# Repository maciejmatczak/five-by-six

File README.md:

# five-by-six
`five-by-six` is a split keyboard design which tries to meet this goals:
- 5x6 keys per half (so [let's split](https://github.com/climbalima/let-s-Split-v2) with a number row)
- dual side pcb
- case design done in parametrical manner, in a CAD software
- high automations/scripting for predictable and reproducible results

## Table of content
- [five-by-six](#five-by-six)
  - [Table of content](#table-of-content)
- [Description](#description)
  - [PCB](#pcb)
  - [Case](#case)
  - [Automations](#automations)
  - [Development setup](#development-setup)
  - [Workflow](#workflow)

# Description
## PCB
PCB is designed in KiCAD with help of 3rd party libraries from [keebio](https://github.com/keebio) (components and footprints). Can't thank enough for battle tested, dual sided switch footprints. Keys are set in matrix of pitch 19.05mm. Arduino Pro Micro is placed on outside edge, jack is placed on the inside.

## Case
Case is designed in FreeCAD to achieve pure mechanical, parametrical description. Exported DXF (Autodesk DXF 2D(\*.dxf)) of every element is later manually imported in a clean KiCad's PCB as edge cuts. After that, every circle is replaced with a proper mounting hole.

Master sketch approach was used, learned with mr Ha Gei's [video](https://www.youtube.com/watch?v=8Bmcgn2RBGI).

## Automations
All the actions are held in `tasks.py` files which are handled by [invoke](http://www.pyinvoke.org/). Case and PCB designs has it's own `tasks.py` which are design specific. Global one is used for creating fabrication files.

Plotting scripts are based on [plotter](https://github.com/akshmakov/pcbops_template/blob/master/kicad_cicd/plotter.py) from [Andrey Shmakov](https://github.com/akshmakov). He also gave a nice talk during KiCon 2019 ([video](https://www.youtube.com/watch?v=cQ-iFtBBwFc)).

`circles_to_holes.py` was created to easily transfer FreeCAD design hole data to mounting holes/drill information.

## Development setup
This software versions was used:
 - KiCad 5.1.2
 - FreeCAD 0.18
 - Python 3.7 (though >= 3.6 should be fine)

Clone the repository, download submodules:
```
git submodule update --init --recursive
```

Under Linux environment (at least for Manjaro and KiCad from official packages) KiCad's python packages are setup for system wide python. The easiest way to install dependencies is to:
```
pip install -r requirements.txt --user
```

Create .env file in root directory with path to KiCad's MountingHole library being set as in example:
```
KICAD_MOUNTING_HOLE_PATH = '/usr/share/kicad/modules/MountingHole.pretty'
```

## Workflow
Short description of step by step procedure of development:
 - case:
   - design case and pcb contour in FreeCAD
   - export designs to DXFs
   - load case DXFs into empty KiCad projects, save, close
   - while being under `five-by-six/case` directory, run `inv circle-to-holes`, which would exchange every circle to proper M2 padded mounting hole
 - pcb:
   - design schematic, open pcb
   - load pcb contour DXF from case design
   - route PCB
   - run `inv circle-to-holes` which would exchange circles to 5mm drill holes (for standoffs)
 - fabrication files
   - in root directory run `inv plot-all`; all gerbers should be plotted, zipped + some basic documentation and preview pdfs created as well

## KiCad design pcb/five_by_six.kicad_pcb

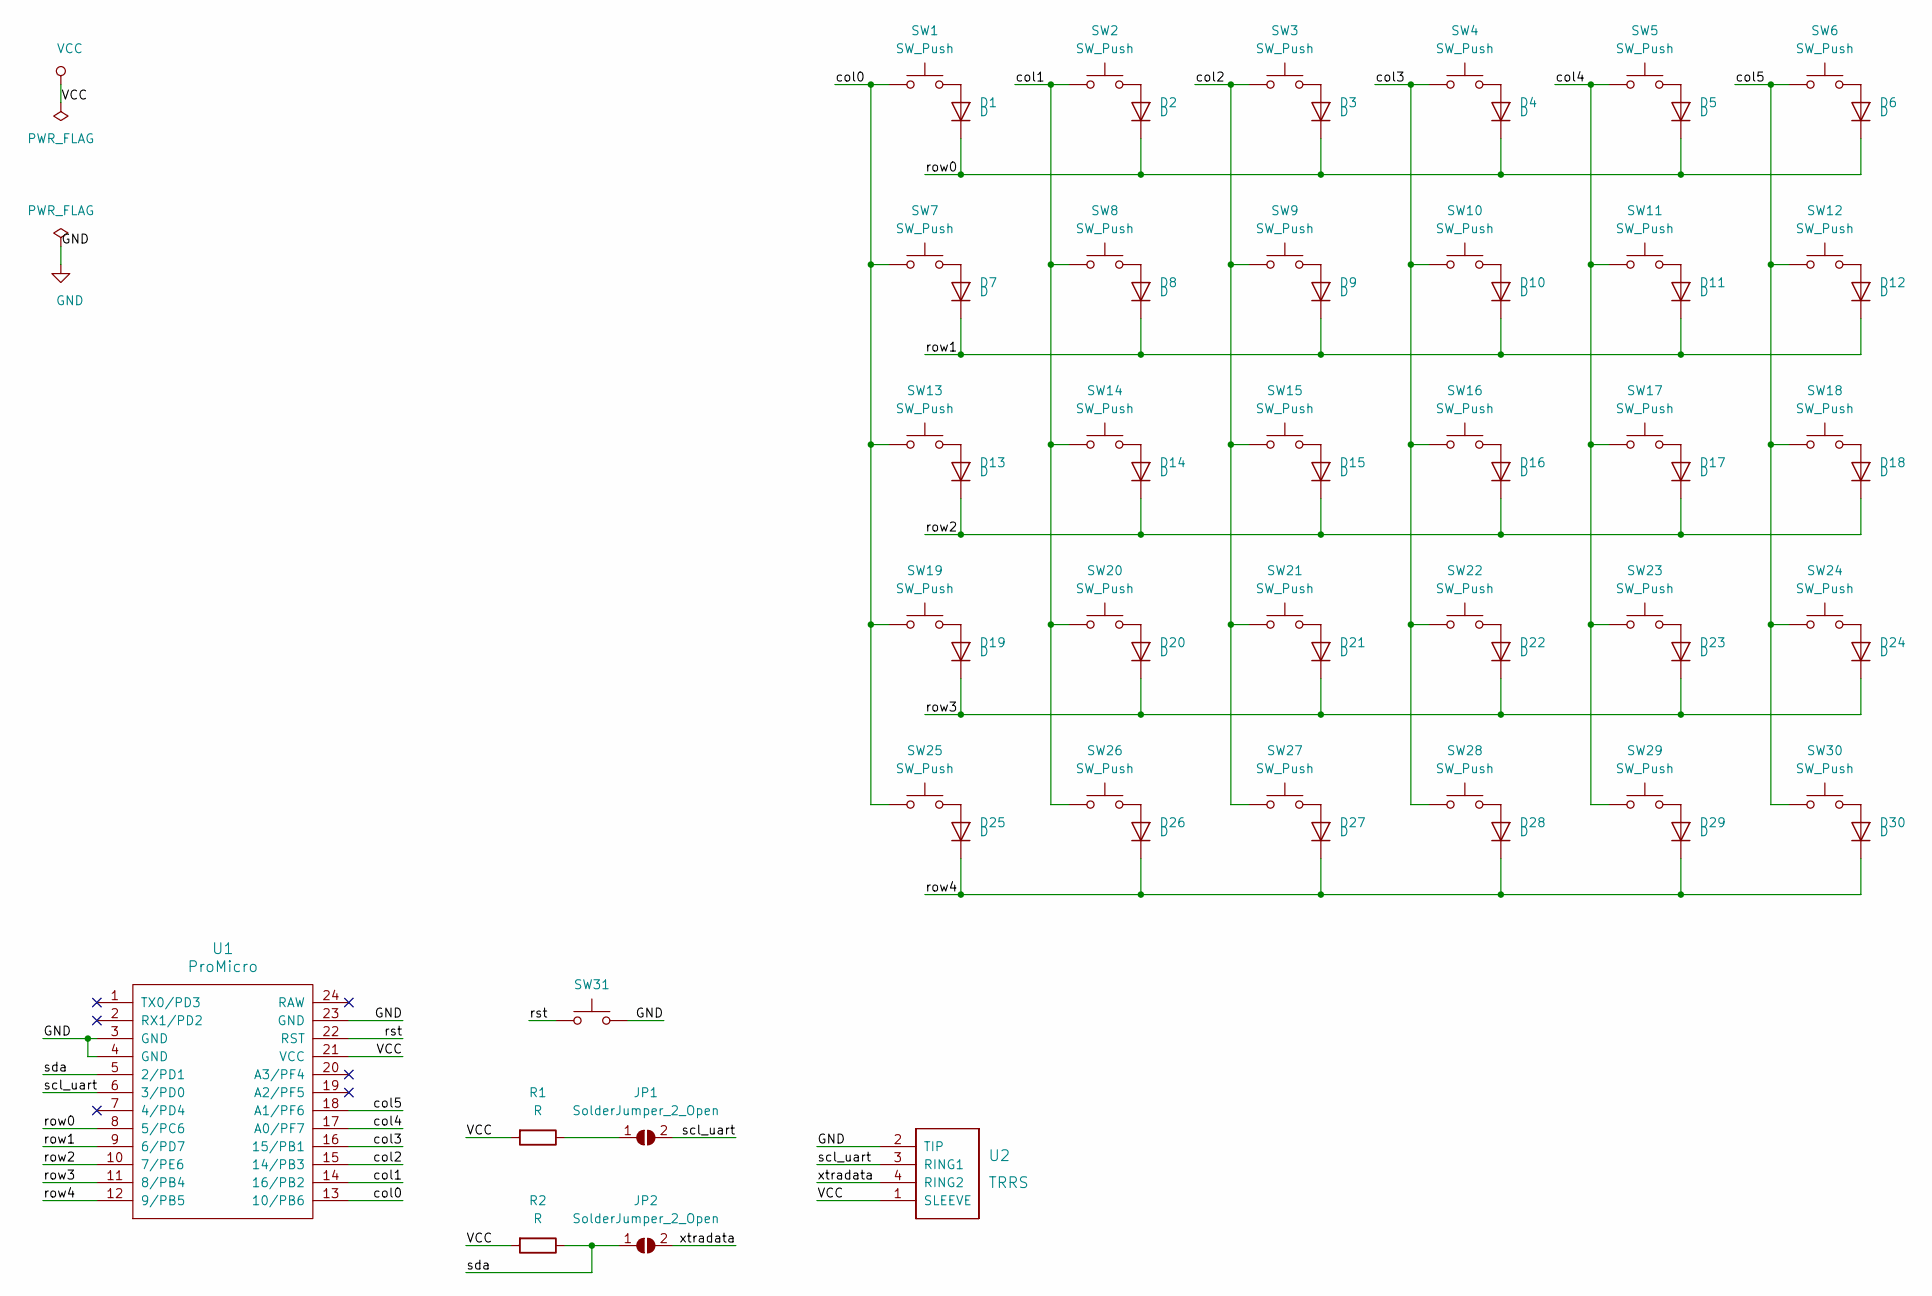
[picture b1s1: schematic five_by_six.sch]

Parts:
D1, D2, D3, D4, D5, D6, D7, D8, D9, D10, D11, D12, D13, D14, D15, D16, D17, D18, D19, D20, D21, D22, D23, D24, D25, D26, D27, D28, D29, D30: D; Diode-dual
JP1, JP2: SolderJumper_2_Open; SolderJumper-2_P1.3mm_Open_RoundedPad1.0x1.5mm
R1, R2: R; Resistor-Hybrid
SW1, SW2, SW3, SW4, SW5, SW6, SW7, SW8, SW9, SW10, SW11, SW12, SW13, SW14, SW15, SW16, SW17, SW18, SW19, SW20, SW21, SW22, SW23, SW24, SW25, SW26, SW27, SW28, SW29, SW30: SW_Push; Hybrid_PCB_100H_Dual_hole
SW31: MX; SW_PUSH_6mm_H7.3mm
U1: ProMicro; ArduinoProMicro
U2: TRRS; TRRS-PJ-320A-dual

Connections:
/col0: SW1.1, SW7.1, SW13.1, SW19.1, SW25.1, U1.13 (10/PB6)
/col1: SW2.1, SW8.1, SW14.1, SW20.1, SW26.1, U1.14 (16/PB2)
/col2: SW3.1, SW9.1, SW15.1, SW21.1, SW27.1, U1.15 (14/PB3)
/col3: SW4.1, SW10.1, SW16.1, SW22.1, SW28.1, U1.16 (15/PB1)
/col4: SW5.1, SW11.1, SW17.1, SW23.1, SW29.1, U1.17 (A0/PF7)
/col5: SW6.1, SW12.1, SW18.1, SW24.1, SW30.1, U1.18 (A1/PF6)
/row0: D1.1 (K), D2.1 (K), D3.1 (K), D4.1 (K), D5.1 (K), D6.1 (K), U1.8 (5/PC6)
/row1: D7.1 (K), D8.1 (K), D9.1 (K), D10.1 (K), D11.1 (K), D12.1 (K), U1.9 (6/PD7)
/row2: D13.1 (K), D14.1 (K), D15.1 (K), D16.1 (K), D17.1 (K), D18.1 (K), U1.10 (7/PE6)
/row3: D19.1 (K), D20.1 (K), D21.1 (K), D22.1 (K), D23.1 (K), D24.1 (K), U1.11 (8/PB4)
/row4: D25.1 (K), D26.1 (K), D27.1 (K), D28.1 (K), D29.1 (K), D30.1 (K), U1.12 (9/PB5)
/rst: SW31.1, U1.22 (RST)
/scl_uart: JP1.2 (B), U1.6 (3/PD0), U2.3 (RING1)
/sda: JP2.1 (A), R2.1, U1.5 (2/PD1)
/xtradata: JP2.2 (B), U2.4 (RING2)
GND: SW31.2, U1.3 (GND), U1.4 (GND), U1.23 (GND), U2.2 (TIP)
unnamed: D1.2 (A), SW1.2
unnamed: D2.2 (A), SW2.2
unnamed: D3.2 (A), SW3.2
unnamed: D4.2 (A), SW4.2
unnamed: D5.2 (A), SW5.2
unnamed: D6.2 (A), SW6.2
unnamed: D7.2 (A), SW7.2
unnamed: D8.2 (A), SW8.2
unnamed: D9.2 (A), SW9.2
unnamed: D10.2 (A), SW10.2
unnamed: D11.2 (A), SW11.2
unnamed: D12.2 (A), SW12.2
unnamed: D13.2 (A), SW13.2
unnamed: D14.2 (A), SW14.2
unnamed: D15.2 (A), SW15.2
unnamed: D16.2 (A), SW16.2
unnamed: D17.2 (A), SW17.2
unnamed: D18.2 (A), SW18.2
unnamed: D19.2 (A), SW19.2
unnamed: D20.2 (A), SW20.2
unnamed: D21.2 (A), SW21.2
unnamed: D22.2 (A), SW22.2
unnamed: D23.2 (A), SW23.2
unnamed: D24.2 (A), SW24.2
unnamed: D25.2 (A), SW25.2
unnamed: D26.2 (A), SW26.2
unnamed: D27.2 (A), SW27.2
unnamed: D28.2 (A), SW28.2
unnamed: D29.2 (A), SW29.2
unnamed: D30.2 (A), SW30.2
unnamed: JP1.1 (A), R1.1
VCC: R1.2, R2.2, U1.21 (VCC), U2.1 (SLEEVE)

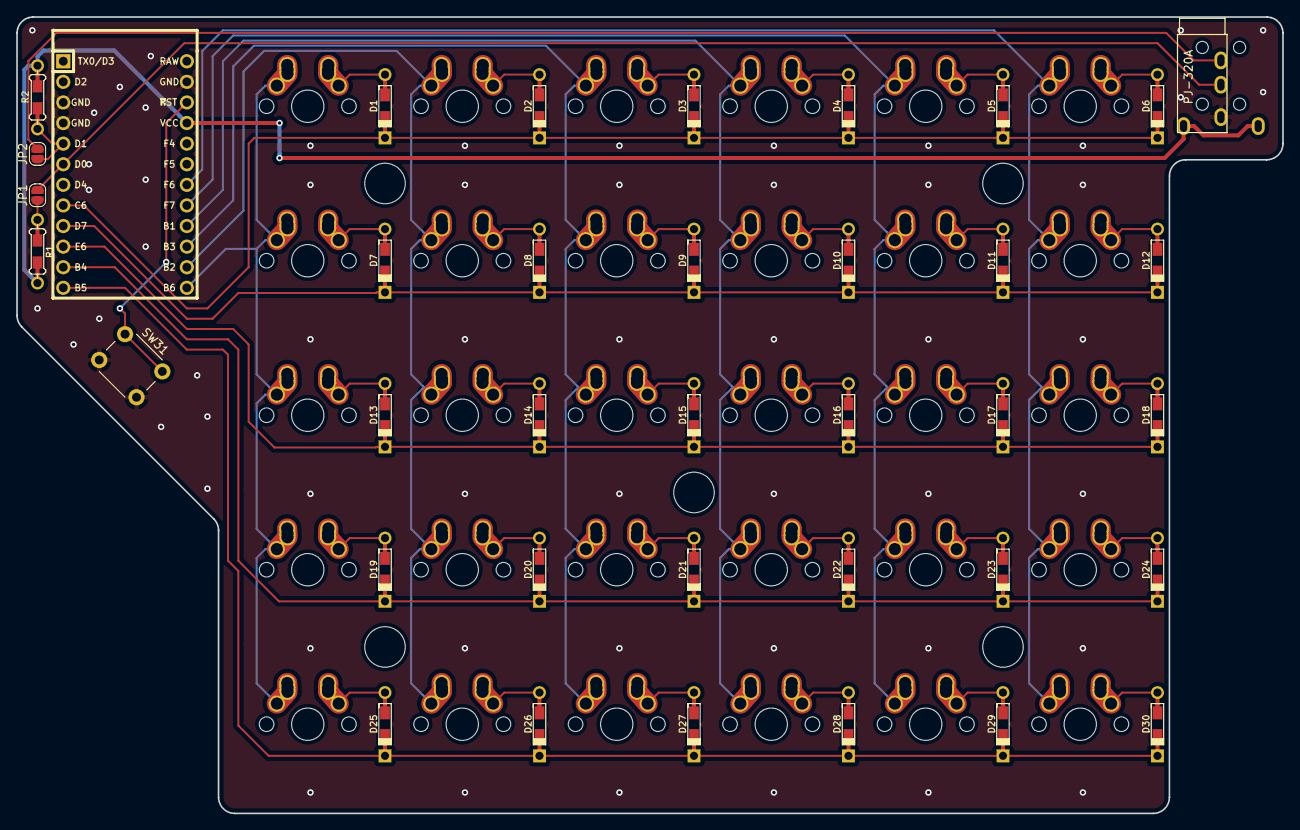
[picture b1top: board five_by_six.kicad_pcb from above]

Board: 2 copper layers, 156.1 x 98.2 mm, 67 parts (0 on the bottom side), 48 nets.

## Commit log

2019-08-09 Add keebio modules
2019-08-09 Add case design files
2019-08-09 Add gitignore
2019-08-09 Add initial python requirements
2019-08-09 Add pcb design
2019-08-09 Add pcb key switches placer helper
2019-08-09 Add initial tasks
2019-08-09 Removing keyswitches submodule
2019-08-09 Removing modules
2019-08-09 Readd keebio-components
2019-08-09 Readd Keebio-Parts.pretty
2019-08-09 Clean up
2019-08-10 Create LICENSE
2019-08-10 Add plot scripts for doc and fab files
2019-08-10 Add plot setup for every pcb in the project
2019-08-10 Add FAB dir
2019-08-10 Add python-dotenv
2019-08-10 Add plot setup
2019-08-10 Add linter setup
2019-08-10 Add mounting holes
2019-08-10 Add circles to holes helper
    Every circle is changed into a mounting hole module
2019-08-10 Generate DXFs
2019-08-10 Add case's kicad project with only edge cuts
2019-08-10 Add tasks.py for case pcbs
2019-08-10 Circles to holes
2019-08-10 Correct typo ic to uc
2019-08-10 Move preview pdfs to fab plotter
2019-08-10 Add readme
2019-08-10 Correct slug and zipping naming
2019-08-10 Styling
2019-08-10 Typos, rephrasing
2019-08-10 Add reset hole in uc cover
2019-08-10 Fix zipping issue
    Every next zipp was including full fab files...
